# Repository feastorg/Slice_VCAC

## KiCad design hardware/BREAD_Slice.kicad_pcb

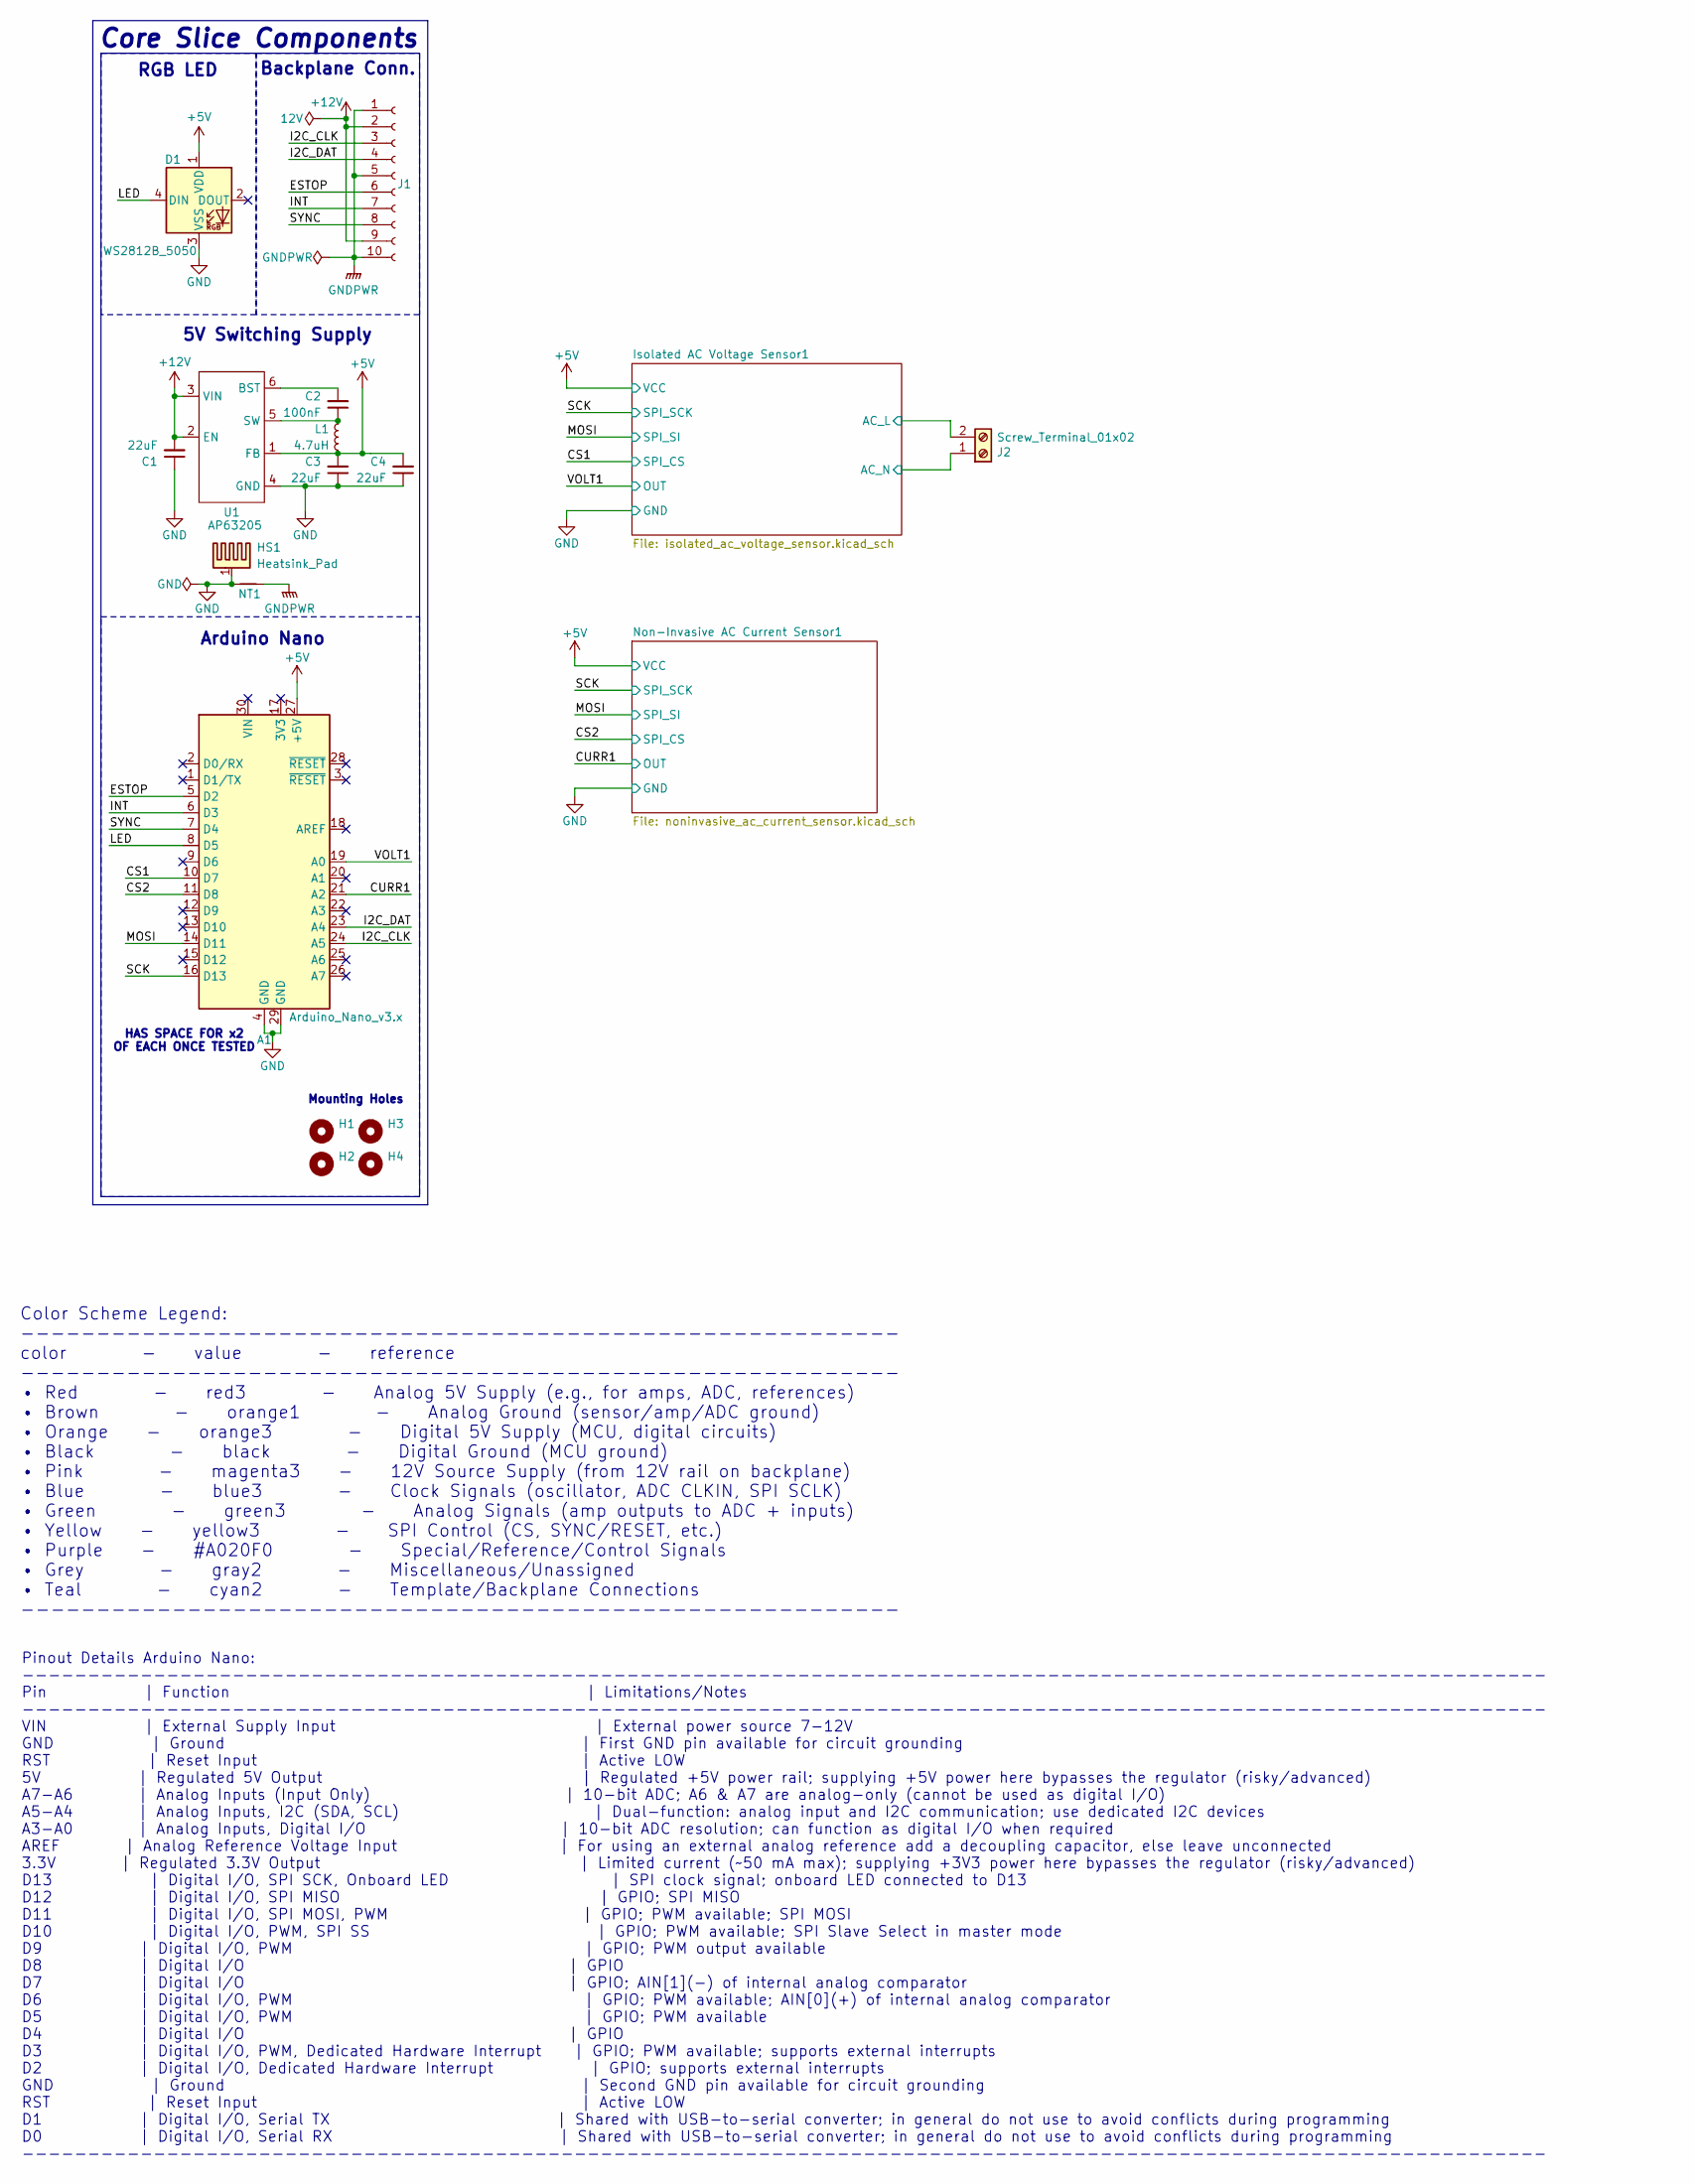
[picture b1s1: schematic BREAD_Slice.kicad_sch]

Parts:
A1: Arduino_Nano_v3.x; Arduino_Nano
C1, C3, C4: 22uF; C_1206_3216Metric
C2: 100nF; C_1206_3216Metric
D1: WS2812B_5050; WS2812-5050-4PIN
H1, H2, H3, H4: MountingHole; MountingHole_5mm
HS1: Heatsink_Pad; Thermal Pad
J1: Conn_01x10_Socket; PinSocket_1x10_P2.54mm_Horizontal
J2: Screw_Terminal_01x02; TerminalBlock_4Ucon_1x02_P3.50mm_Horizontal
L1: 4.7uH; L_1210_3225Metric
NT1: NetTie_2; NetTie-2_SMD_Pad2.0mm
U1: AP63205; SOIC_05WU-7_DIO

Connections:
+5V: A1.27 (+5V), C3.2, C4.2, D1.1 (VDD), L1.2, U1.1 (FB); also elsewhere on the board
+12V: C1.2, J1.2, J1.9, U1.2 (EN), U1.3 (VIN)
/CS1: A1.10 (D7); also elsewhere on the board
/CS2: A1.11 (D8); also elsewhere on the board
/CURR1: A1.21 (A2); also elsewhere on the board
/ESTOP: A1.5 (D2), J1.6
/I2C_CLK: A1.24 (A5), J1.3
/I2C_DAT: A1.23 (A4), J1.4
/INT: A1.6 (D3), J1.7
/Isolated AC Voltage Sensor1/AC_L: J2.2; also elsewhere on the board
/Isolated AC Voltage Sensor1/AC_N: J2.1; also elsewhere on the board
/LED: A1.8 (D5), D1.4 (DIN)
/MOSI: A1.14 (D11); also elsewhere on the board
/SCK: A1.16 (D13); also elsewhere on the board
/SYNC: A1.7 (D4), J1.8
/VOLT1: A1.19 (A0); also elsewhere on the board
GND: A1.4 (GND), A1.29 (GND), C1.1, C3.1, C4.1, D1.3 (VSS), HS1.1, NT1.1, U1.4 (GND); also elsewhere on the board
GNDPWR: J1.1, J1.5, J1.10, NT1.2
unnamed: C2.2, U1.6 (BST)
unnamed: C2.1, L1.1, U1.5 (SW)

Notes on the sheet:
5V Switching Supply
HAS SPACE FOR x2 OF EACH ONCE TESTED
Pinout Details Arduino Nano: -------------------------------------------------------------------------------------------------------------------- Pin | Function | Limitations/Notes -------------------------------------------------------------------------------------------------------------------- V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
RGB LED
Color Scheme Legend: ---------------------------------------------------------- color - value - reference ---------------------------------------------------------- • Red - red3 - Analog 5V Supply (e.g., for amps, ADC, references) • Brown - orange1 - Analog Ground (sensor/amp/ADC ground) • Orange -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
Core Slice Components
Arduino Nano
Mounting Holes
Backplane Conn.

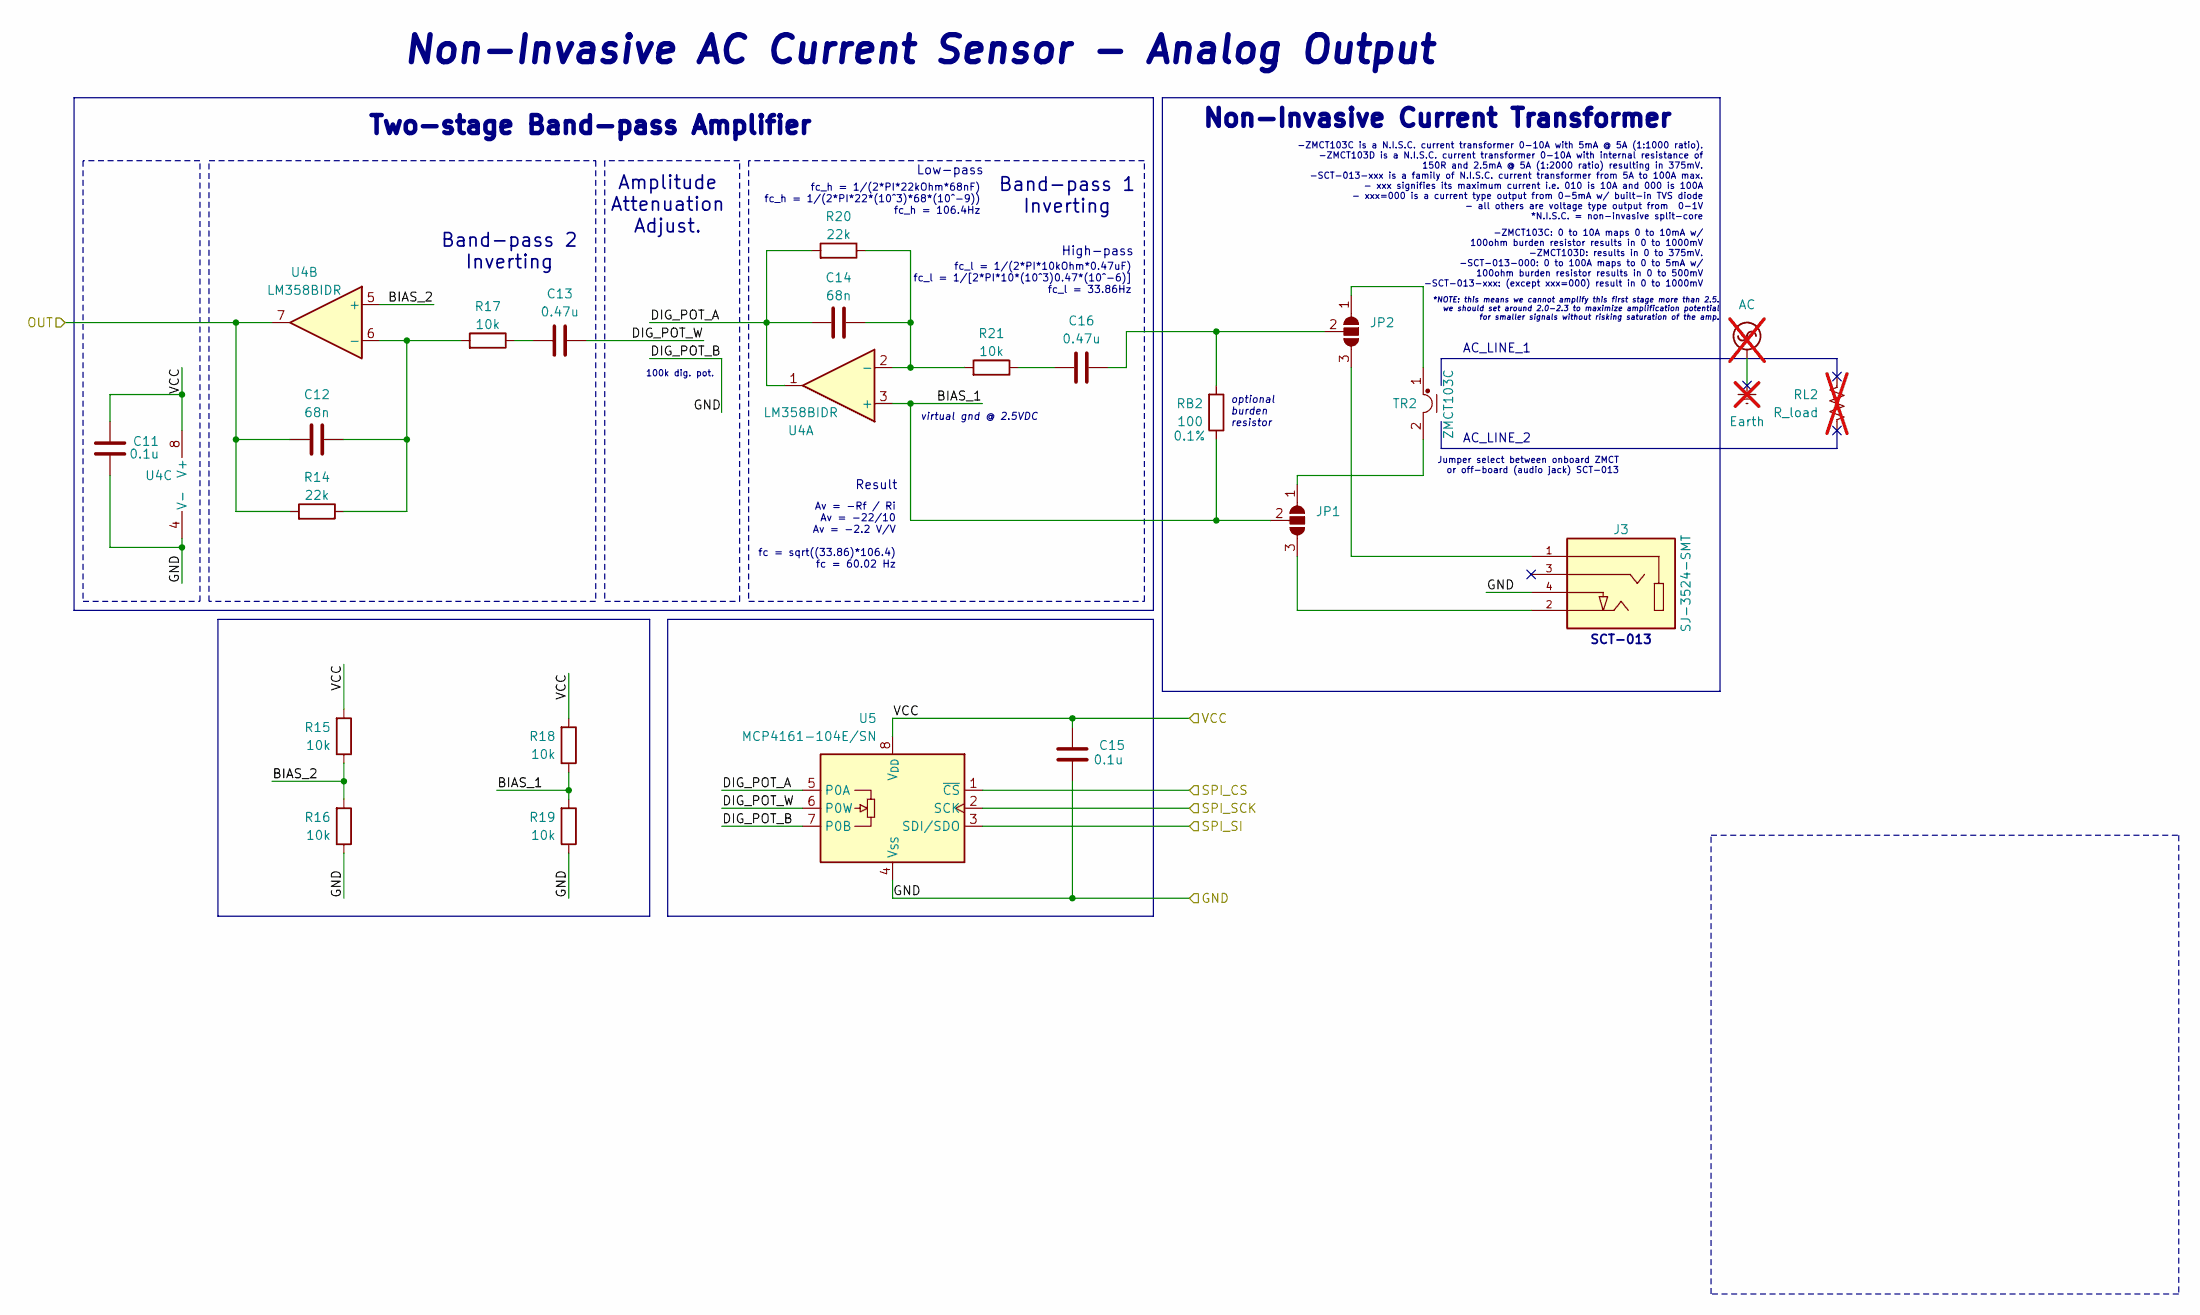
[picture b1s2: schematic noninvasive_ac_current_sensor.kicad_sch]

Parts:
C11, C15: 0.1u; C_0805_2012Metric_Pad1.18x1.45mm_HandSolder
C12, C14: 68n; C_0805_2012Metric_Pad1.18x1.45mm_HandSolder
C13, C16: 0.47u; C_0805_2012Metric_Pad1.18x1.45mm_HandSolder
J3: SJ-3524-SMT; CUI_SJ-3524-SMT; PARTREV 1.03
JP1, JP2: SolderJumper_3_Open; SolderJumper-3_P2.0mm_Open_TrianglePad1.0x1.5mm
R14, R20: 22k; R_0805_2012Metric_Pad1.20x1.40mm_HandSolder
R15, R16, R17, R18, R19, R21: 10k; R_0805_2012Metric_Pad1.20x1.40mm_HandSolder
RB2: 100; R_0805_2012Metric_Pad1.20x1.40mm_HandSolder
RL2: R_load; not fitted
TR2: ZMCT103C; Transformer_Zeming_ZMCT103C
U4: LM358BIDR; SOIC-8_3.9x4.9mm_P1.27mm
U5: MCP4161-104E/SN; SOIC-8_3.9x4.9mm_P1.27mm

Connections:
+5V: C11.2, C15.2, R15.2, R18.2, U4.8 (V+), U5.8 (V_{DD}); also elsewhere on the board
/CS2: U5.1 (~CS); also elsewhere on the board
/CURR1: C12.2, R14.2, U4.7; also elsewhere on the board
/MOSI: U5.3 (SDI/SDO); also elsewhere on the board
/Non-Invasive AC Current Sensor1/BIAS_1: JP1.2 (C), R18.1, R19.2, RB2.1, U4.3 (+)
/Non-Invasive AC Current Sensor1/BIAS_2: R15.1, R16.2, U4.5 (+)
/Non-Invasive AC Current Sensor1/DIG_POT_A: C14.2, R20.2, U4.1, U5.5 (P0A)
/Non-Invasive AC Current Sensor1/DIG_POT_W: C13.1, U5.6 (P0W)
/SCK: U5.2 (SCK); also elsewhere on the board
GND: C11.1, C15.1, J3.4, R16.1, R19.1, U4.4 (V-), U5.4 (V_{SS}), U5.7 (P0B); also elsewhere on the board
unnamed: C13.2, R17.1
unnamed: C16.2, R21.1
unnamed: JP1.1 (A), TR2.2
unnamed: J3.2, JP1.3 (B)
unnamed: JP2.1 (A), TR2.1
unnamed: J3.1, JP2.3 (B)
unnamed: C16.1, JP2.2 (C), RB2.2
unnamed: C14.1, R20.1, R21.2, U4.2 (-)
unnamed: C12.1, R14.1, R17.2, U4.6 (-)

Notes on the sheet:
-ZMCT103C: 0 to 10A maps 0 to 10mA w/ 100ohm burden resistor results in 0 to 1000mV -ZMCT103D: results in 0 to 375mV. -SCT-013-000: 0 to 100A maps to 0 to 5mA w/ 100ohm burden resistor results in 0 to 500mV -SCT-013-xxx: (except xxx=000) result in 0 to 1000mV
Band-pass 2 Inverting
Amplitude Attenuation Adjust.
Jumper select between onboard ZMCT or off-board (audio jack) SCT-013
fc_l = 1/(2*PI*10kOhm*0.47uF) fc_l = 1/[2*PI*10*(10^3)0.47*(10^-6)] fc_l = 33.86Hz
AC_LINE_2
*NOTE: this means we cannot amplify this first stage more than 2.5. we should set around 2.0-2.3 to maximize amplification potential for smaller signals without risking saturation of the amp.
Low-pass
optional burden resistor
100k dig. pot.
Result
virtual gnd @ 2.5VDC
Non-Invasive Current Transformer
Two-stage Band-pass Amplifier
-ZMCT103C is a N.I.S.C. current transformer 0-10A with 5mA @ 5A (1:1000 ratio). -ZMCT103D is a N.I.S.C. current transformer 0-10A with internal resistance of 150R and 2.5mA @ 5A (1:2000 ratio) resulting in 375mV. -SCT-013-xxx is a family of N.I.S.C. current transformer from 5A to 100A max. - xxx si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
High-pass
AC_LINE_1
Av = -Rf / Ri Av = -22/10 Av = -2.2 V/V fc = sqrt((33.86)*106.4) fc = 60.02 Hz
Non-Invasive AC Current Sensor - Analog Output
Band-pass 1 Inverting
SCT-013
fc_h = 1/(2*PI*22kOhm*68nF) fc_h = 1/(2*PI*22*(10^3)*68*(10^-9)) fc_h = 106.4Hz

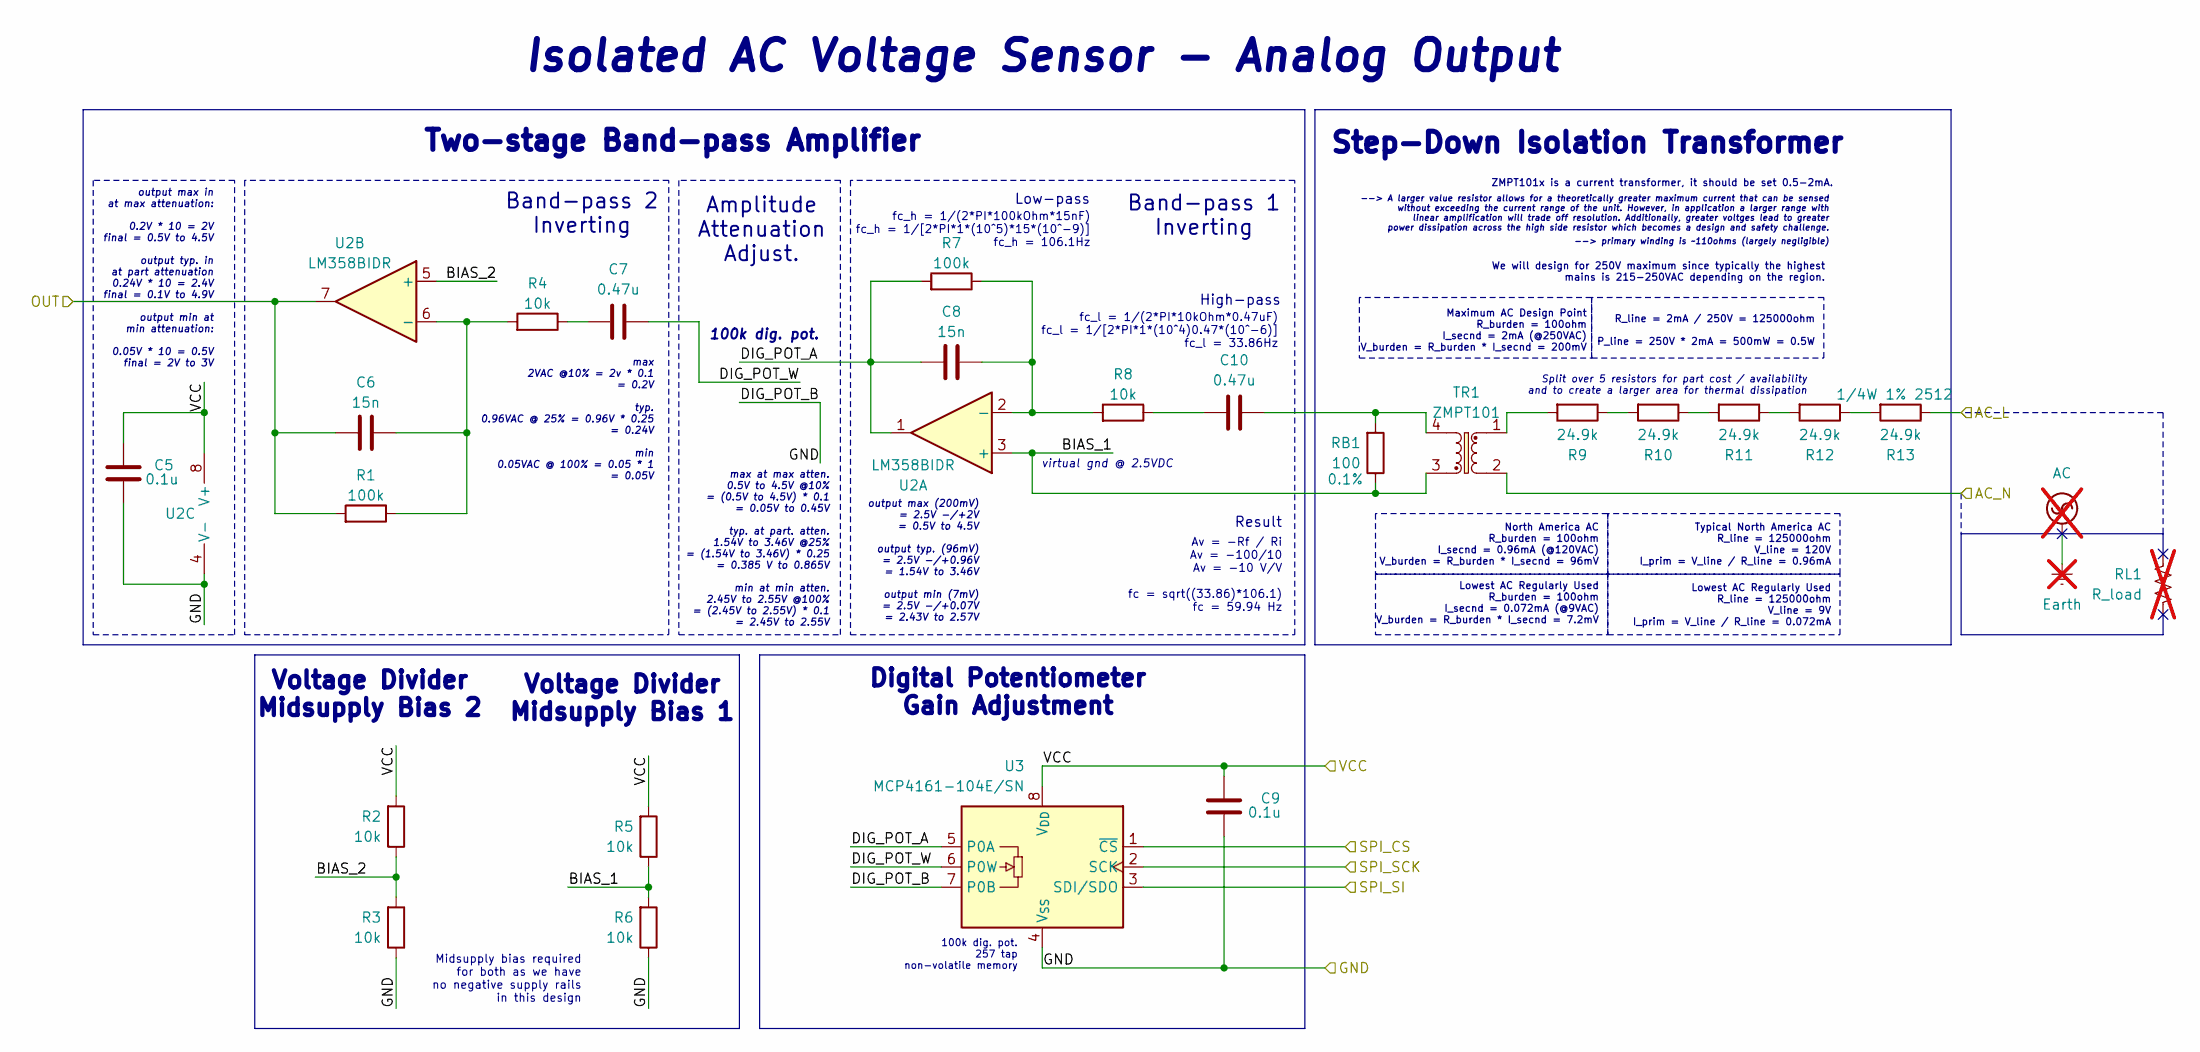
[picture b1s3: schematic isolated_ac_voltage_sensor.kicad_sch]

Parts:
C5, C9: 0.1u; C_0805_2012Metric_Pad1.18x1.45mm_HandSolder
C6, C8: 15n; C_0805_2012Metric_Pad1.18x1.45mm_HandSolder
C7, C10: 0.47u; C_0805_2012Metric_Pad1.18x1.45mm_HandSolder
R1, R7: 100k; R_0805_2012Metric_Pad1.20x1.40mm_HandSolder
R2, R3, R4, R5, R6, R8: 10k; R_0805_2012Metric_Pad1.20x1.40mm_HandSolder
R9, R10, R11, R12, R13: 24.9k; R_1206_3216Metric_Pad1.30x1.75mm_HandSolder
RB1: 100; R_0805_2012Metric_Pad1.20x1.40mm_HandSolder
RL1: R_load; not fitted
TR1: ZMPT101; Transformer_Zeming_ZMPT101K
U2: LM358BIDR; SOIC-8_3.9x4.9mm_P1.27mm
U3: MCP4161-104E/SN; SOIC-8_3.9x4.9mm_P1.27mm

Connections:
+5V: C5.2, C9.2, R2.2, R5.2, U2.8 (V+), U3.8 (V_{DD}); also elsewhere on the board
/CS1: U3.1 (~CS); also elsewhere on the board
/Isolated AC Voltage Sensor1/AC_L: R13.1; also elsewhere on the board
/Isolated AC Voltage Sensor1/AC_N: TR1.2; also elsewhere on the board
/Isolated AC Voltage Sensor1/BIAS_1: R5.1, R6.2, RB1.1, TR1.3, U2.3 (+)
/Isolated AC Voltage Sensor1/BIAS_2: R2.1, R3.2, U2.5 (+)
/Isolated AC Voltage Sensor1/DIG_POT_A: C8.2, R7.2, U2.1, U3.5 (P0A)
/Isolated AC Voltage Sensor1/DIG_POT_W: C7.1, U3.6 (P0W)
/MOSI: U3.3 (SDI/SDO); also elsewhere on the board
/SCK: U3.2 (SCK); also elsewhere on the board
/VOLT1: C6.2, R1.2, U2.7; also elsewhere on the board
GND: C5.1, C9.1, R3.1, R6.1, U2.4 (V-), U3.4 (V_{SS}), U3.7 (P0B); also elsewhere on the board
unnamed: C7.2, R4.1
unnamed: C10.1, RB1.2, TR1.4
unnamed: C10.2, R8.1
unnamed: R9.2, TR1.1
unnamed: R10.1, R11.2
unnamed: R9.1, R10.2
unnamed: R11.1, R12.2
unnamed: R12.1, R13.2
unnamed: C8.1, R7.1, R8.2, U2.2 (-)
unnamed: C6.1, R1.1, R4.2, U2.6 (-)

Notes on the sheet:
Split over 5 resistors for part cost / availability and to create a larger area for thermal dissipation
Lowest AC Regularly Used R_burden = 100ohm I_secnd = 0.072mA (@9VAC) V_burden = R_burden * I_secnd = 7.2mV
Band-pass 1 Inverting
We will design for 250V maximum since typically the highest mains is 215-250VAC depending on the region.
ZMPT101x is a current transformer, it should be set 0.5-2mA.
max 2VAC @10% = 2v * 0.1 = 0.2V typ. 0.96VAC @ 25% = 0.96V * 0.25 = 0.24V min 0.05VAC @ 100% = 0.05 * 1 = 0.05V
Av = -Rf / Ri Av = -100/10 Av = -10 V/V fc = sqrt((33.86)*106.1) fc = 59.94 Hz
virtual gnd @ 2.5VDC
100k dig. pot. 257 tap non-volatile memory
100k dig. pot.
output max in at max attenuation: 0.2V * 10 = 2V final = 0.5V to 4.5V output typ. in at part attenuation 0.24V * 10 = 2.4V final = 0.1V to 4.9V output min at min attenuation: 0.05V * 10 = 0.5V final = 2V to 3V
Digital Potentiometer Gain Adjustment
fc_l = 1/(2*PI*10kOhm*0.47uF) fc_l = 1/[2*PI*1*(10^4)0.47*(10^-6)] fc_l = 33.86Hz
Typical North America AC R_line = 125000ohm V_line = 120V I_prim = V_line / R_line = 0.96mA
High-pass
max at max atten. 0.5V to 4.5V @10% = (0.5V to 4.5V) * 0.1 = 0.05V to 0.45V typ. at part. atten. 1.54V to 3.46V @25% = (1.54V to 3.46V) * 0.25 = 0.385 V to 0.865V min at min atten. 2.45V to 2.55V @100% = (2.45V to 2.55V) * 0.1 = 2.45V to 2.55V
Two-stage Band-pass Amplifier
Low-pass
Lowest AC Regularly Used R_line = 125000ohm V_line = 9V I_prim = V_line / R_line = 0.072mA
North America AC R_burden = 100ohm I_secnd = 0.96mA (@120VAC) V_burden = R_burden * I_secnd = 96mV
Maximum AC Design Point R_burden = 100ohm I_secnd = 2mA (@250VAC) V_burden = R_burden * I_secnd = 200mV
--> primary winding is ~110ohms (largely negligible)
fc_h = 1/(2*PI*100kOhm*15nF) fc_h = 1/[2*PI*1*(10^5)*15*(10^-9)] fc_h = 106.1Hz
Amplitude Attenuation Adjust.
Voltage Divider Midsupply Bias 2
Isolated AC Voltage Sensor - Analog Output
Midsupply bias required for both as we have no negative supply rails in this design
Band-pass 2 Inverting
R_line = 2mA / 250V = 125000ohm P_line = 250V * 2mA = 500mW = 0.5W
--> A larger value resistor allows for a theoretically greater maximum current that can be sensed without exceeding the current range of the unit. However, in application a larger range with linear amplification will trade off resolution. Additionally, greater voltges lead to greater power dissipat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
output max (200mV) = 2.5V -/+2V = 0.5V to 4.5V output typ. (96mV) = 2.5V -/+0.96V = 1.54V to 3.46V output min (7mV) = 2.5V -/+0.07V = 2.43V to 2.57V
Step-Down Isolation Transformer
Result
Voltage Divider Midsupply Bias 1

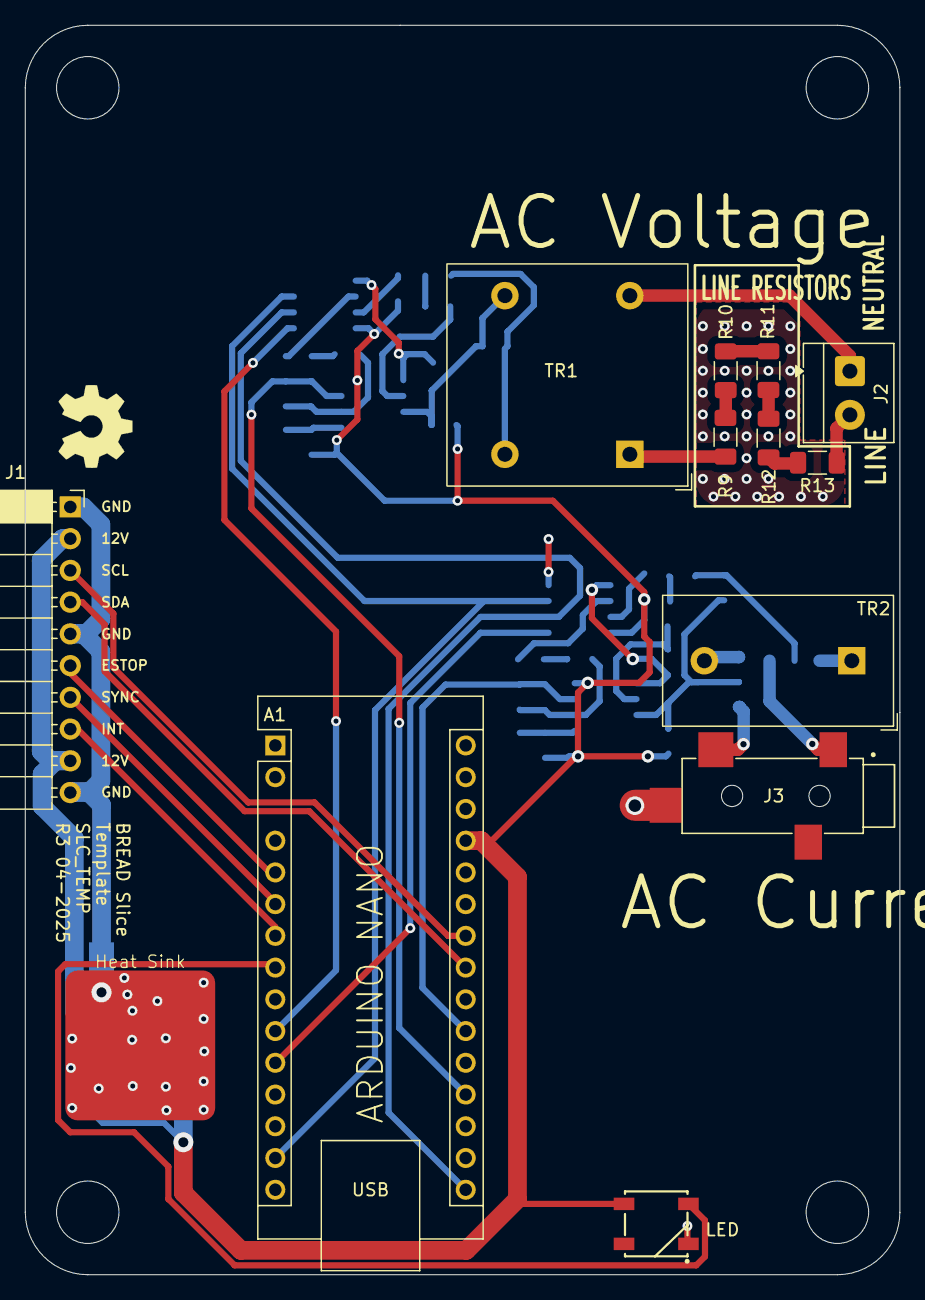
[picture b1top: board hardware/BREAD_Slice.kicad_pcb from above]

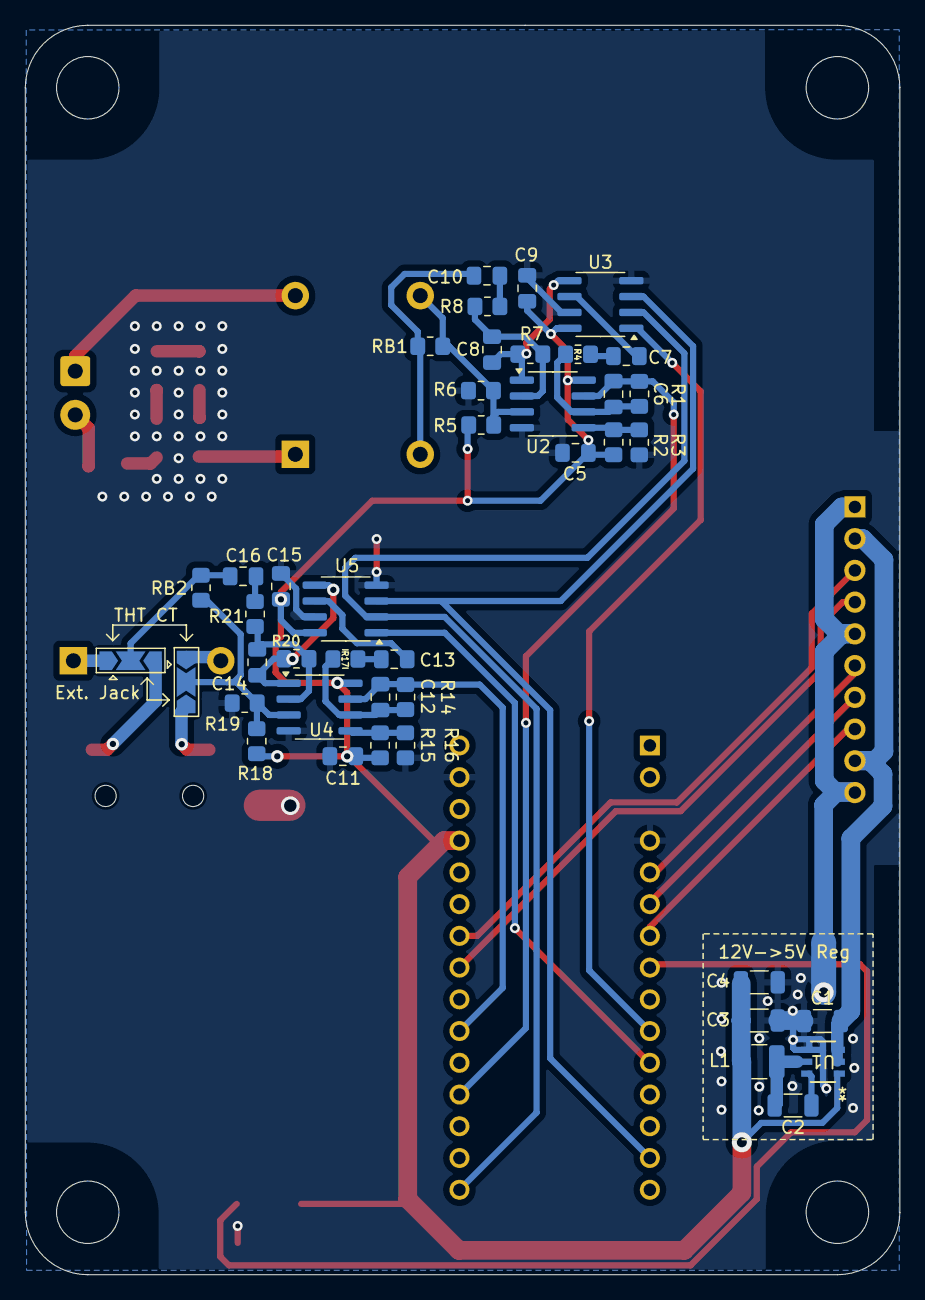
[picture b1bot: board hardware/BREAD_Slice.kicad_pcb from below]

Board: 2 copper layers, 70.0 x 100.0 mm, 61 parts (43 on the bottom side), 47 nets.

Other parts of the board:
Logo1: Logo_Open_Hardware_Small; OSHW-Symbol_6.7x6mm_SilkScreen

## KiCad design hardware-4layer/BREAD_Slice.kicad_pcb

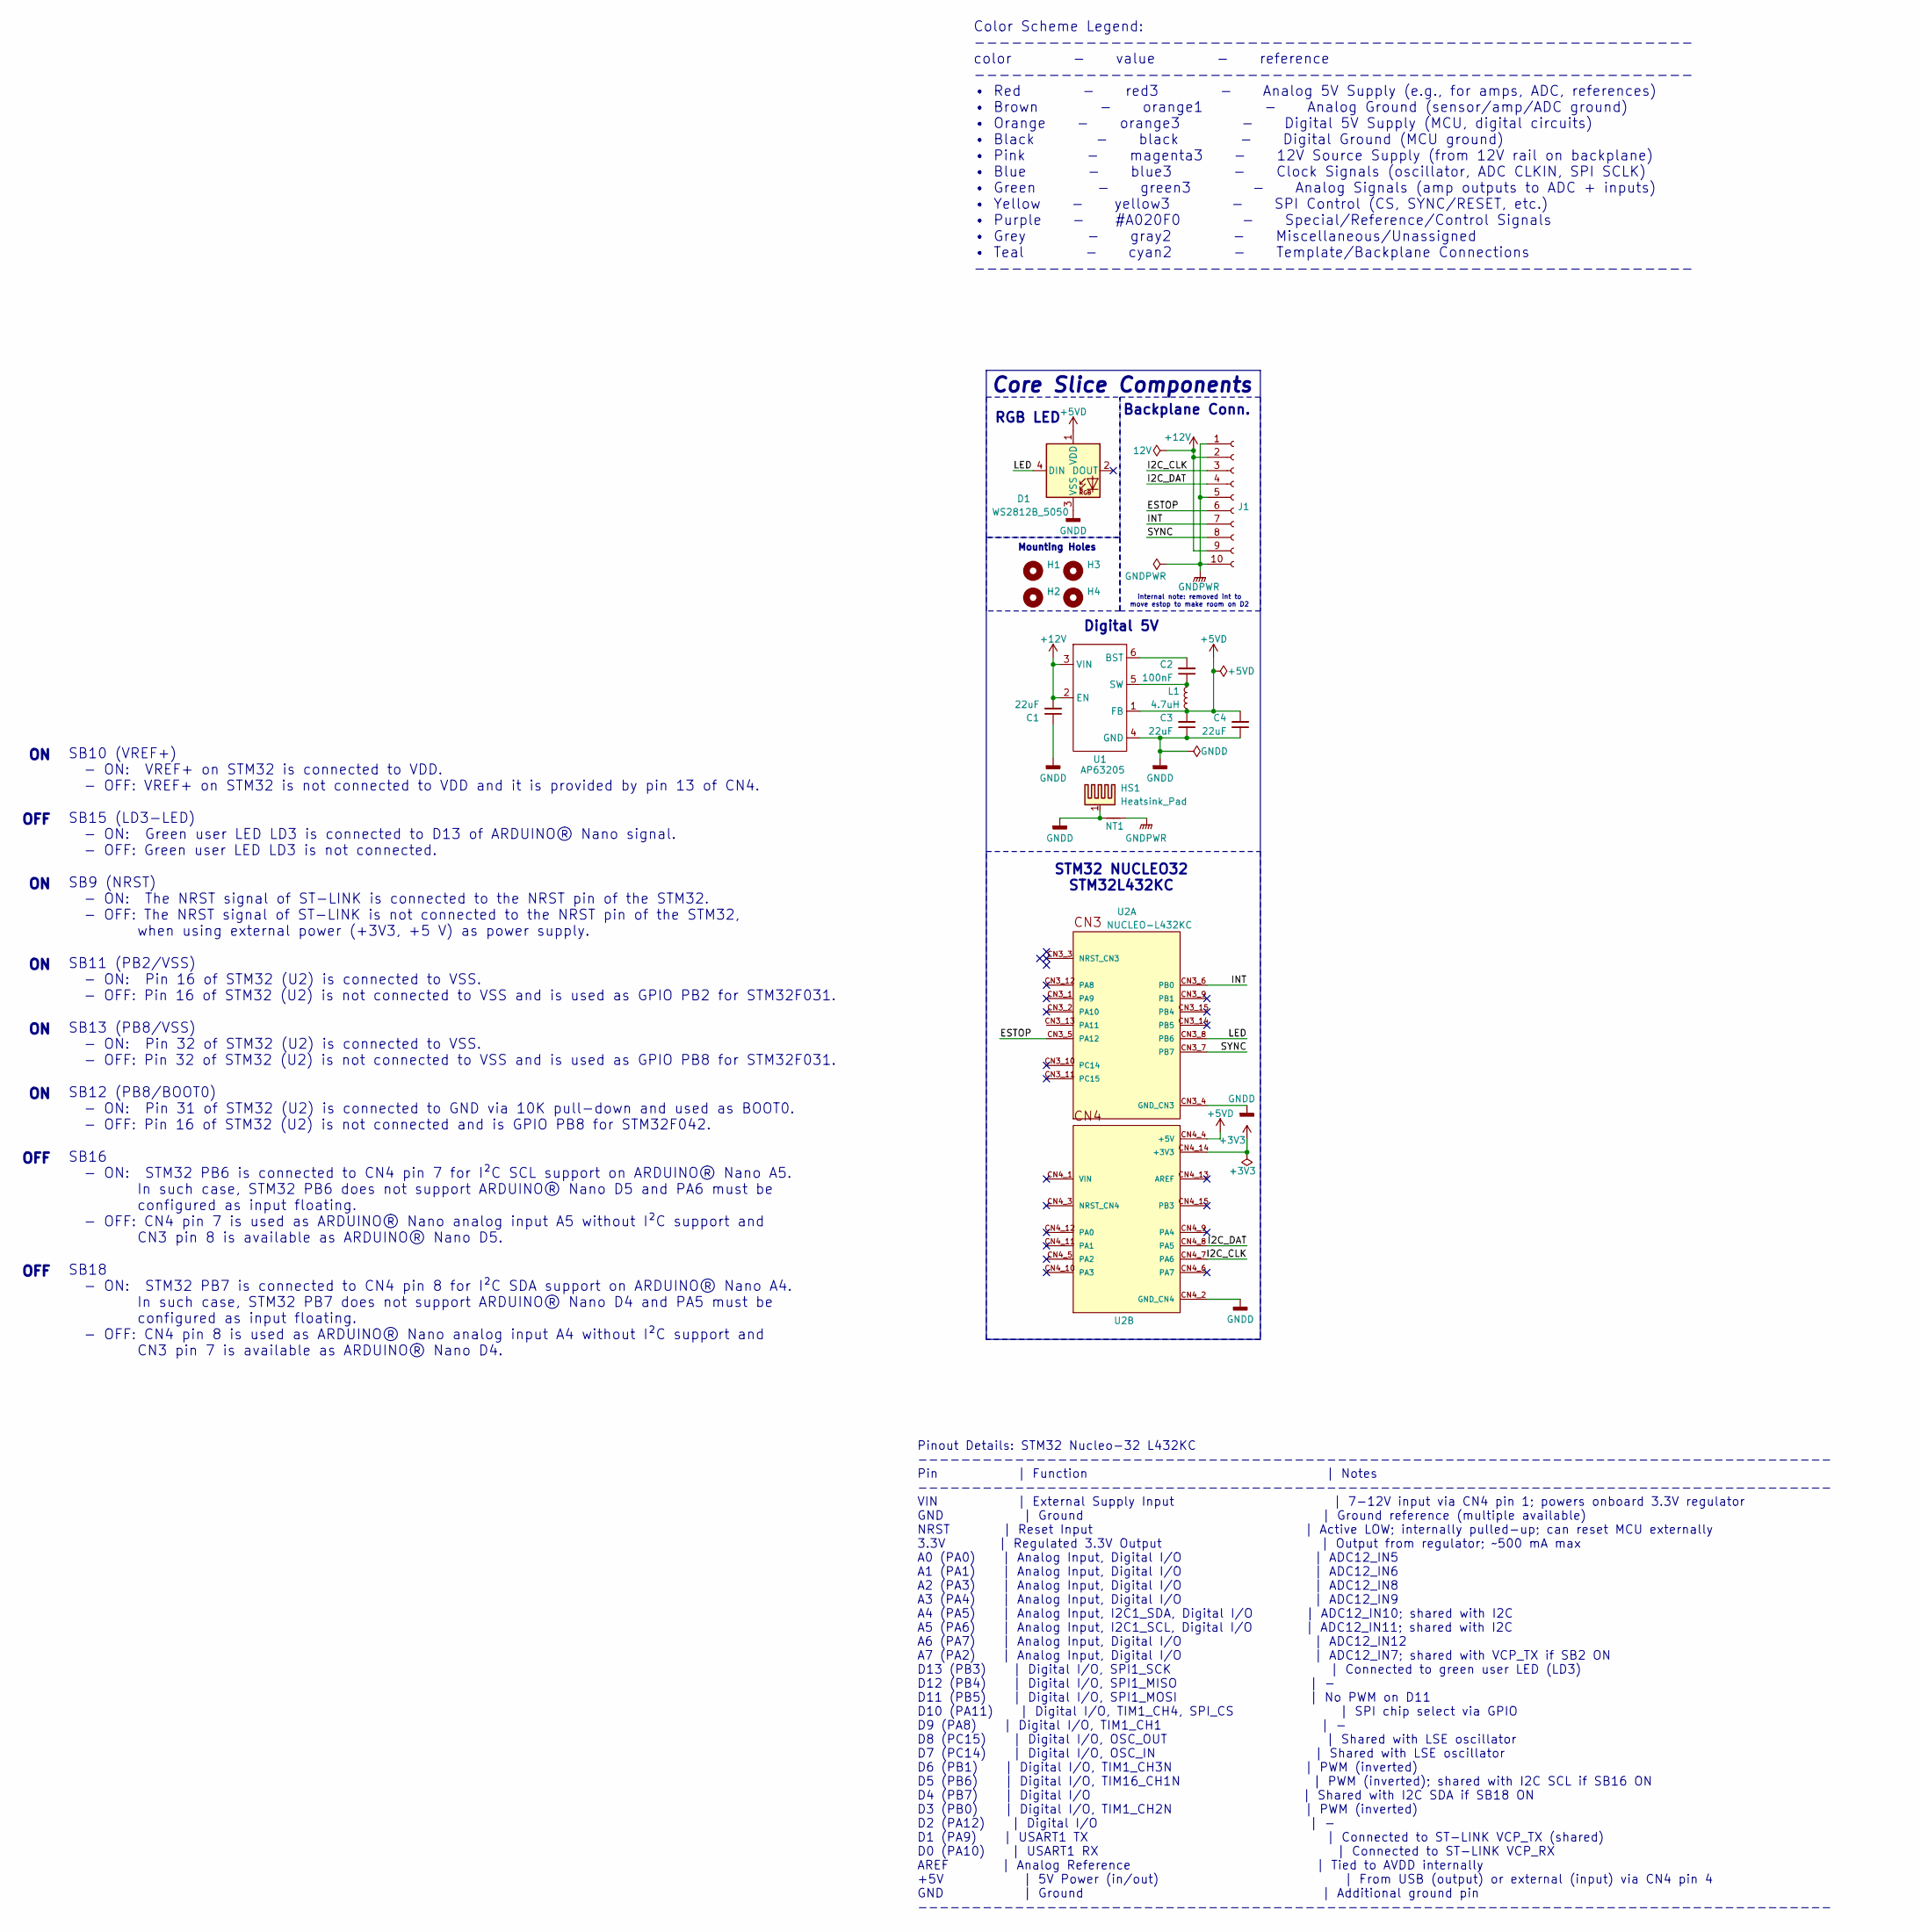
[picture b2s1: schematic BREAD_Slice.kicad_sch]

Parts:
C1, C3, C4: 22uF; C_1206_3216Metric
C2: 100nF; C_1206_3216Metric
D1: WS2812B_5050; WS2812-5050-4PIN
H1, H2, H3, H4: MountingHole; MountingHole_5mm
HS1: Heatsink_Pad; Thermal Pad
J1: Conn_01x10_Female; PinSocket_1x10_P2.54mm_Horizontal
L1: 4.7uH; L_1210_3225Metric
NT1: NetTie_2; NetTie-2_SMD_Pad2.0mm
U1: AP63205; TSOT-23-6
U2: NUCLEO-L432KC; MODULE_NUCLEO-L432KC; PARTREV N/A

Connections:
+3V3: U2.CN4_14 (+3V3)
+5VD: C3.2, C4.2, D1.1 (VDD), L1.2, U1.1 (FB), U2.CN4_4 (+5V)
+12V: C1.2, J1.2, J1.9, U1.2 (EN), U1.3 (VIN)
/ESTOP: J1.6, U2.CN3_5 (PA12)
/I2C_CLK: J1.3, U2.CN4_7 (PA6)
/I2C_DAT: J1.4, U2.CN4_8 (PA5)
/INT: J1.7, U2.CN3_6 (PB0)
/LED: D1.4 (DIN), U2.CN3_8 (PB6)
/SYNC: J1.8, U2.CN3_7 (PB7)
GNDD: C1.1, C3.1, C4.1, D1.3 (VSS), HS1.1, NT1.1, U1.4 (GND), U2.CN3_4 (GND_CN3), U2.CN4_2 (GND_CN4)
GNDPWR: J1.1, J1.5, J1.10, NT1.2
unnamed: C2.2, U1.6 (BST)
unnamed: C2.1, L1.1, U1.5 (SW)

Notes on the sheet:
ON OFF ON ON ON ON OFF OFF
internal note: removed int to move estop to make room on D2
Backplane Conn.
Color Scheme Legend: ---------------------------------------------------------- color - value - reference ---------------------------------------------------------- • Red - red3 - Analog 5V Supply (e.g., for amps, ADC, references) • Brown - orange1 - Analog Ground (sensor/amp/ADC ground) • Orange -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
Core Slice Components
SB10 (VREF+) - ON: VREF+ on STM32 is connected to VDD. - OFF: VREF+ on STM32 is not connected to VDD and it is provided by pin 13 of CN4. SB15 (LD3-LED) - ON: Green user LED LD3 is connected to D13 of ARDUINO® Nano signal. - OFF: Green user LED LD3 is not connected. SB9 (NRST) - ON: The NRST signal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
Digital 5V
STM32 NUCLEO32 STM32L432KC
Pinout Details: STM32 Nucleo-32 L432KC ------------------------------------------------------------------------------------- Pin | Function | Notes ------------------------------------------------------------------------------------- VIN | External Supply Input | 7-12V input via CN4 pin 1; powers o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
RGB LED
Mounting Holes
